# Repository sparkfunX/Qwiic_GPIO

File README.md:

SparkX Qwiic GPIO
=======================================

[*SparkX Qwiic GPIO (SPX-16443)*](https://www.sparkfun.com/products/16443)

TCA9534 breakout board with Qwiic connectors and easy-to-use latch terminals; no longer screw wires into place! Use this board to add more GPIO pins to your system.

Repository Contents
-------------------

* **/Documents** - Contains datasheets and schematic.pdf
* **/Hardware** - Current .brd and .sch files for product
* **/Software** - Examples to get started with Qwiic GPIO

License Information
-------------------

This product is _**open source**_!

Please review the LICENSE.md file for license information.

If you have any questions or concerns on licensing, please contact technical support on our [SparkFun forums](https://forum.sparkfun.com/viewforum.php?f=152).

Distributed as-is; no warranty is given.

- Your friends at SparkFun.

_<COLLABORATION CREDIT>_

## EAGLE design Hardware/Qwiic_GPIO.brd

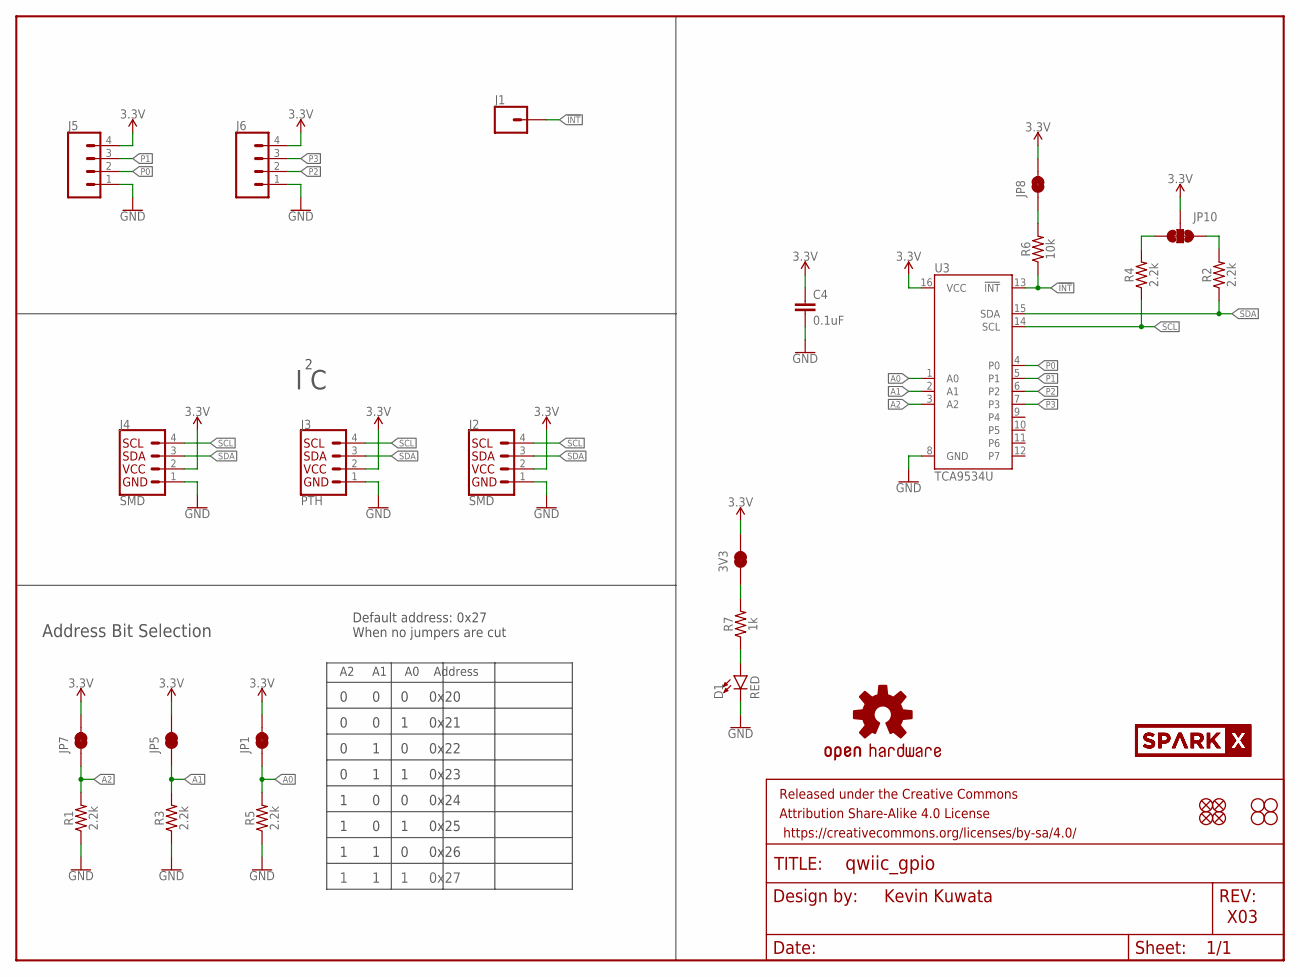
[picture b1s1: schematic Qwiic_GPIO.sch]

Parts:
3V3: JUMPER-SMT_2_NC_TRACE_SILK; SMT-JUMPER_2_NC_TRACE_SILK
C4: 0.1uF; 0603
D1: RED; LED-0603
FD1, FD2: FIDUCIAL1X2; FIDUCIAL-1X2
FRAME1: FRAME-LETTER; CREATIVE_COMMONS
H1, H2: STAND-OFF
J1: CONN_01PTH_NO_SILK_YES_STOP; 1X01_NO_SILK
J2, J4: SMD; 1X04_1MM_RA
J3: PTH; 1X04_NO_SILK
J5, J6: CONN_04LATCH; LATCHTERMINAL-5MM-4
JP1, JP5, JP7, JP8: JUMPER-SMT_2_NC_TRACE_SILK; SMT-JUMPER_2_NC_TRACE_SILK
JP2, JP6: FIDUCIAL1X2; FIDUCIAL-1X2
JP3, JP4: STAND-OFF
JP10: JUMPER-SMT_3_2-NC_TRACE_SILK; SMT-JUMPER_3_2-NC_TRACE_SILK
LOGO1: OSHW-LOGOMINI; OSHW-LOGO-MINI
R1, R2, R3, R4, R5: 2.2k; 0603
R6: 10k; 0603
R7: 1k; 0603
U3: TCA9534U; 16SOIC
U$1, U$2: SPARKX-LOGO3; SPARKX-SMALL

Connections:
3.3V: 3V3.2, C4.1, J2.2 (VCC), J3.2 (VCC), J4.2 (VCC), J5.4, J6.4, JP1.2, JP5.2, JP7.2, JP8.2, JP10.2, U3.16 (VCC)
!INT: J1.1, R6.1, U3.13 (!INT)
A0: JP1.1, R5.2, U3.1 (A0)
A1: JP5.1, R3.2, U3.2 (A1)
A2: JP7.1, R1.2, U3.3 (A2)
GND: C4.2, D1.C, J2.1 (GND), J3.1 (GND), J4.1 (GND), J5.1, J6.1, R1.1, R3.1, R5.1, U3.8 (GND)
unnamed: JP8.1, R6.2
unnamed: D1.A, R7.1
unnamed: 3V3.1, R7.2
P0: J5.2, U3.4 (P0)
P1: J5.3, U3.5 (P1)
P2: J6.2, U3.6 (P2)
P3: J6.3, U3.7 (P3)
SCL: J2.4 (SCL), J3.4 (SCL), J4.4 (SCL), R4.1, U3.14 (SCL)
SCL_PU1: JP10.1, R2.2
SDA: J2.3 (SDA), J3.3 (SDA), J4.3 (SDA), R2.1, U3.15 (SDA)
SDA_PU1: JP10.3, R4.2

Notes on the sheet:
Kevin Kuwata
X03
I C
Address Bit Selection
A2 A1 A0 Address
0 0 0 0x20
0 0 1 0x21
0 1 0 0x22
0 1 1 0x23
1 0 0 0x24
1 0 1 0x25
1 1 0 0x26
1 1 1 0x27
Default address: 0x27 When no jumpers are cut

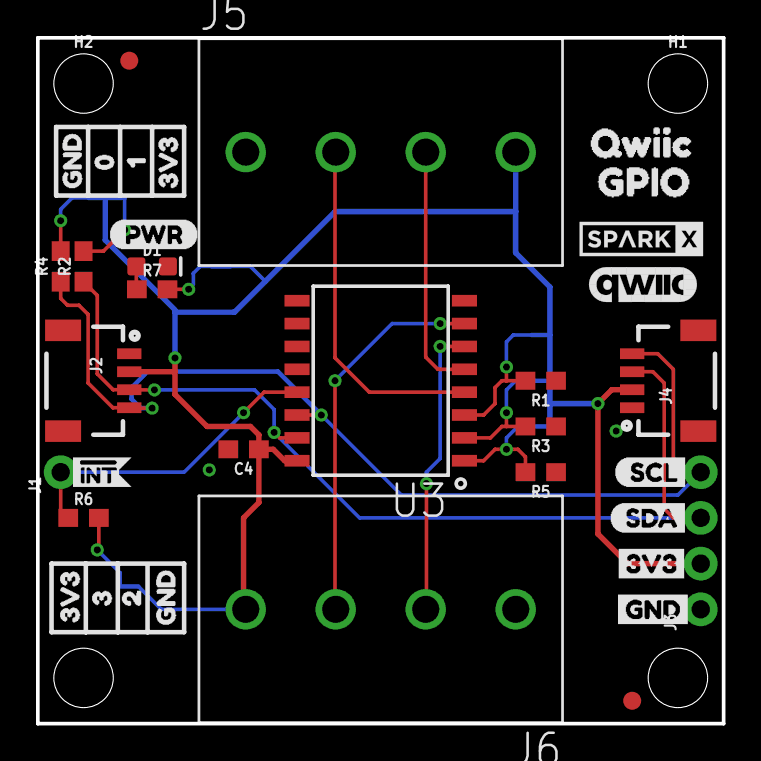
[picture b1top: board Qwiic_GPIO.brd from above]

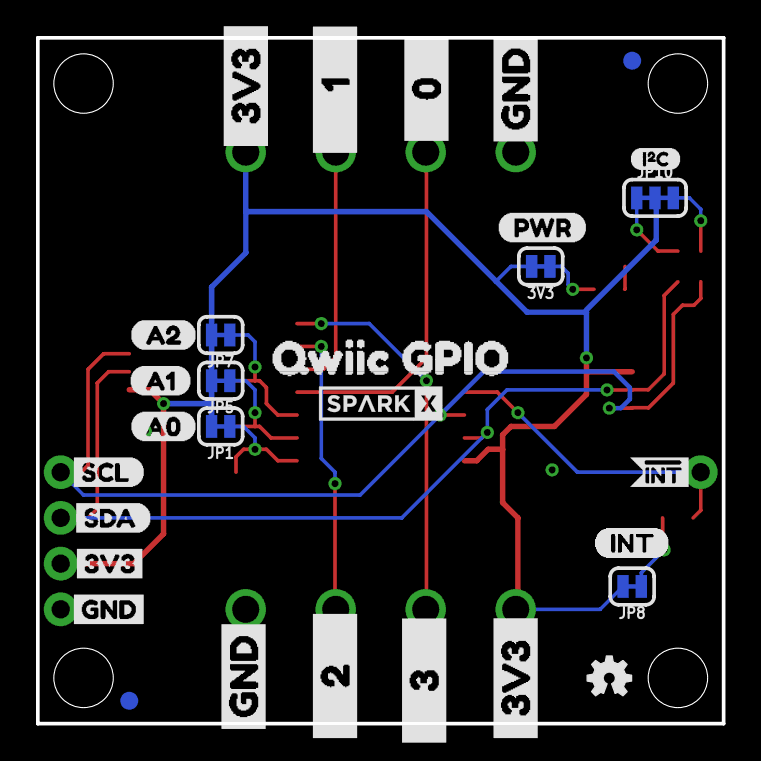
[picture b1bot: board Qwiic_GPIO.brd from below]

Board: 2 copper layers, 38.1 x 38.1 mm, 72 parts (31 on the bottom side), 17 nets.

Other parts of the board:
U$3, U$26, U$38: 3V33
U$5: A11
U$7, U$25: GND4
U$8: QWIIC_GPIO7
U$9: SCL6
U$10: SDA5
U$11: A00
U$12: A21
U$13, U$22: #INT0
U$20: I_SUPER2_C-()-03
U$21: QWIIC_6MM
U$23: SCL0
U$24: SDA1
U$27: 3V32
U$28: GND1
U$29: 15
U$30, U$31: INT1
U$32: QWIIC1
U$33: 20
U$34: 31
U$35: GND2
U$36: GPIO1
U$37: 04
U$39, U$40: PWR0
U$41: ____0____1
U$42: ____2____3
U$43: ____3____4
U$44: _____1____2
U$45, U$46: GND0
U$47, U$48: _3V3_0

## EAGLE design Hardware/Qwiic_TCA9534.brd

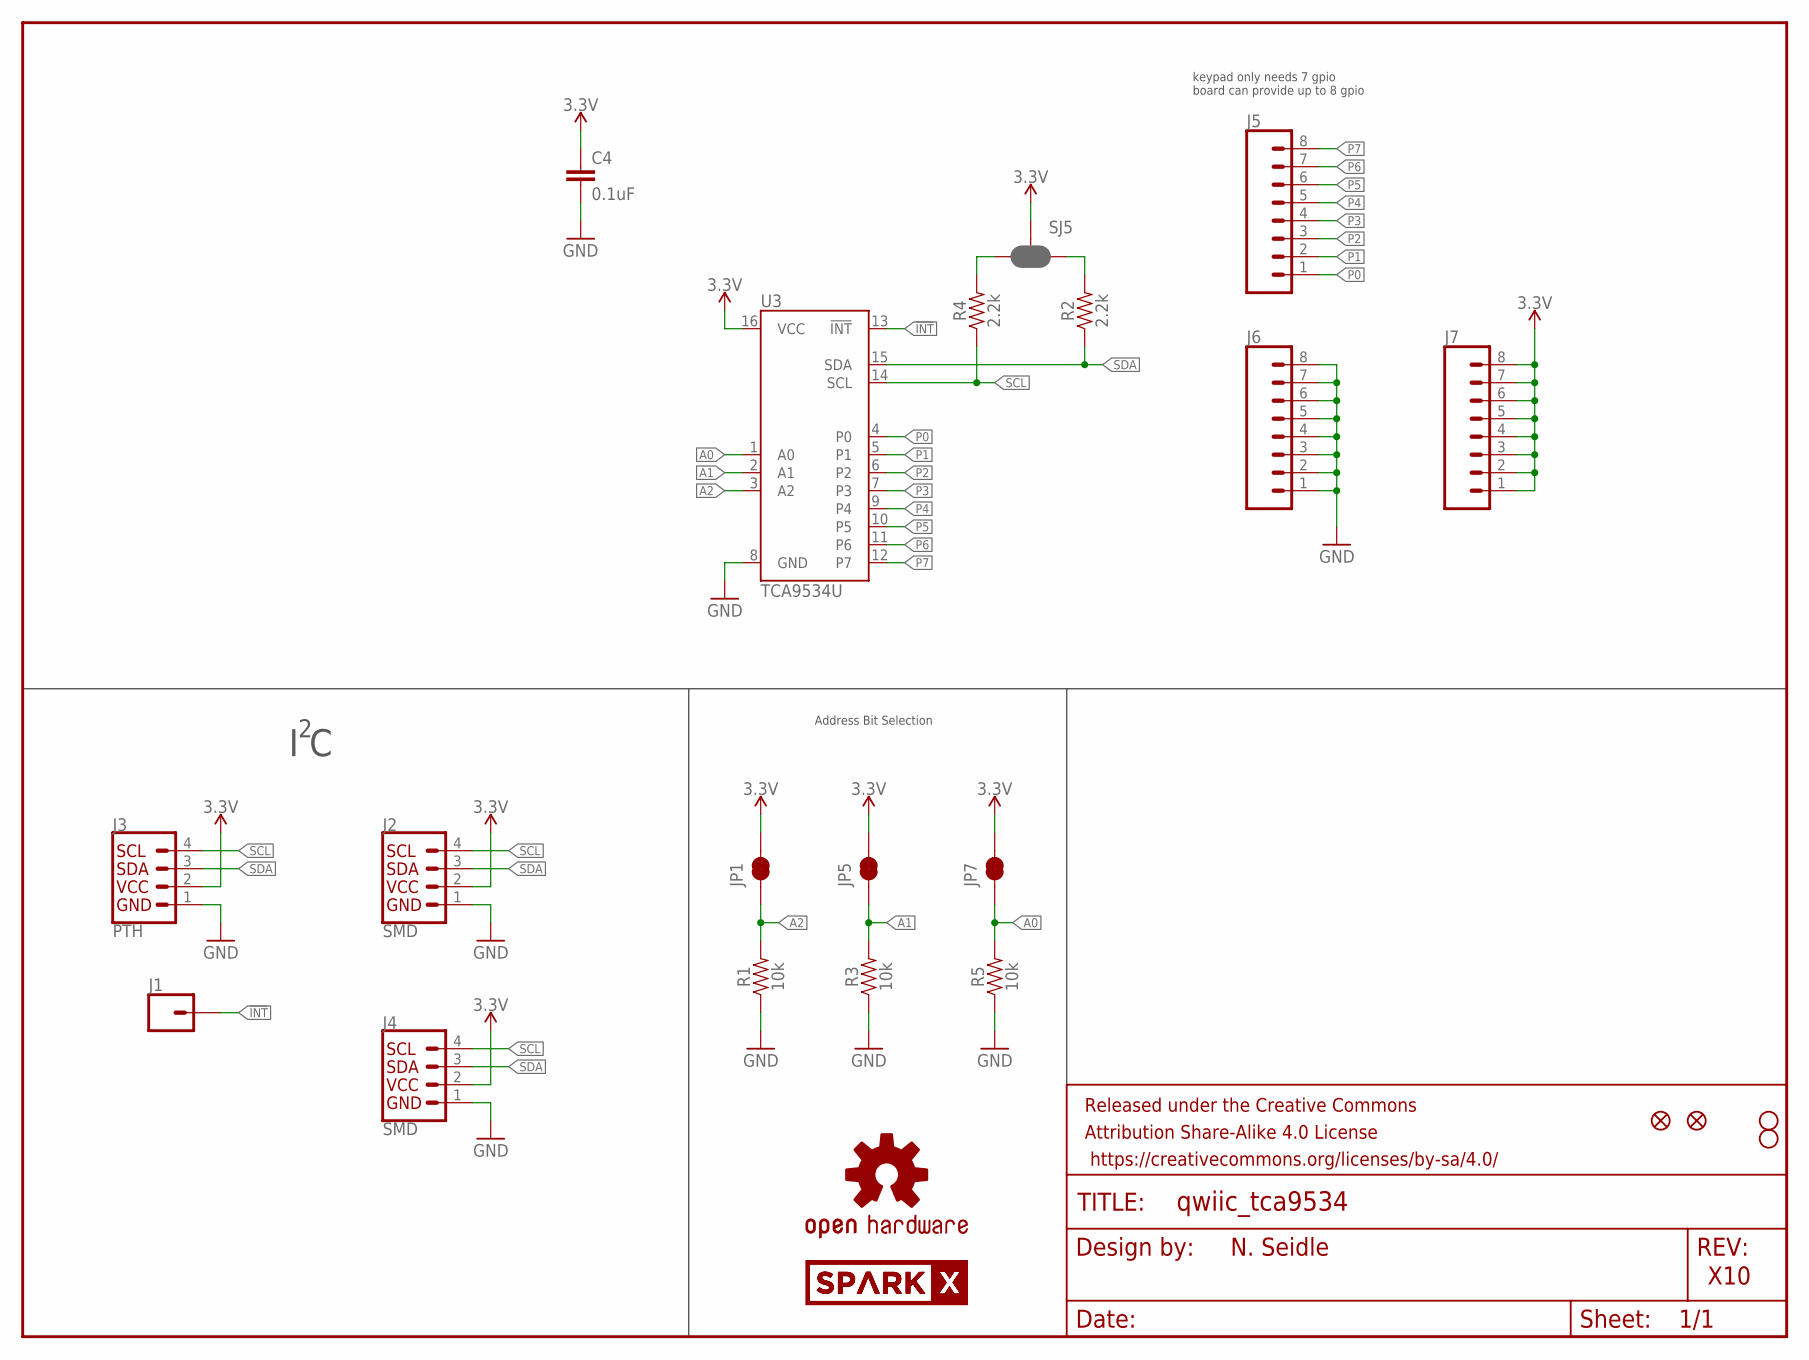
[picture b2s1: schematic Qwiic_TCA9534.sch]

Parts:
C4: 0.1uF; 0603
FRAME1: FRAME-LETTER; CREATIVE_COMMONS
J1: CONN_01PTH_NO_SILK_YES_STOP; 1X01_NO_SILK
J2, J4: SMD; 1X04_1MM_RA
J3: PTH; 1X04_NO_SILK
J5, J6, J7: CONN_08NO_SILK_FEMALE_PTH; 1X08_NO_SILK
JP1, JP5, JP7: JUMPER-SMT_2_NC_TRACE_NO-SILK; SMT-JUMPER_2_NC_TRACE_NO-SILK
JP2, JP6: FIDUCIALUFIDUCIAL; MICRO-FIDUCIAL
JP3, JP4: STAND-OFF
LOGO1: OSHW-LOGOMINI; OSHW-LOGO-MINI
R1, R3, R5: 10k; 0603
R2, R4: 2.2k; 0603
SJ5: SMT-JUMPER-_3-2-NC-PASTE_TALL; SMT-JUMPER_3-2-NC-PASTE_SILK_TALLER_A
U3: TCA9534U; 16SOIC
U$1, U$2: SPARKX-LOGO3; SPARKX-SMALL

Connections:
3.3V: C4.1, J2.2 (VCC), J3.2 (VCC), J4.2 (VCC), J7.1, J7.2, J7.3, J7.4, J7.5, J7.6, J7.7, J7.8, JP1.2, JP5.2, JP7.2, SJ5.2, U3.16 (VCC)
!INT: J1.1, U3.13 (!INT)
A0: JP7.1, R5.2, U3.1 (A0)
A1: JP5.1, R3.2, U3.2 (A1)
A2: JP1.1, R1.2, U3.3 (A2)
GND: C4.2, J2.1 (GND), J3.1 (GND), J4.1 (GND), J6.1, J6.2, J6.3, J6.4, J6.5, J6.6, J6.7, J6.8, R1.1, R3.1, R5.1, U3.8 (GND)
P0: J5.1, U3.4 (P0)
P1: J5.2, U3.5 (P1)
P2: J5.3, U3.6 (P2)
P3: J5.4, U3.7 (P3)
P4: J5.5, U3.9 (P4)
P5: J5.6, U3.10 (P5)
P6: J5.7, U3.11 (P6)
P7: J5.8, U3.12 (P7)
SCL: J2.4 (SCL), J3.4 (SCL), J4.4 (SCL), R4.1, U3.14 (SCL)
SCL_PU1: R2.2, SJ5.1
SDA: J2.3 (SDA), J3.3 (SDA), J4.3 (SDA), R2.1, U3.15 (SDA)
SDA_PU1: R4.2, SJ5.3

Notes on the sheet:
N. Seidle
X10
I C
Address Bit Selection
keypad only needs 7 gpio board can provide up to 8 gpio

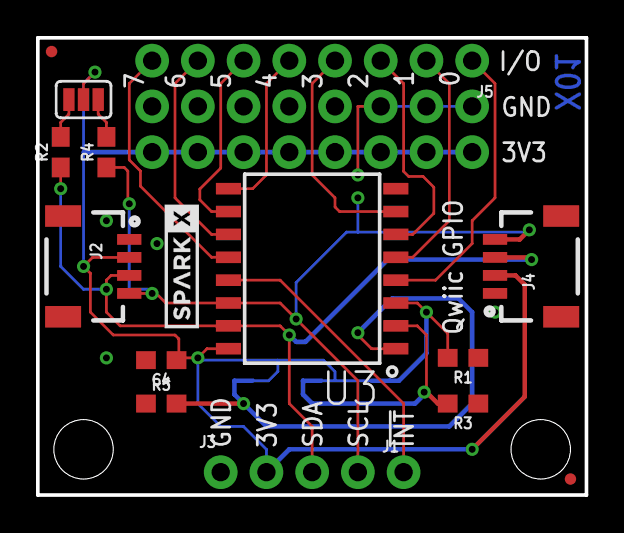
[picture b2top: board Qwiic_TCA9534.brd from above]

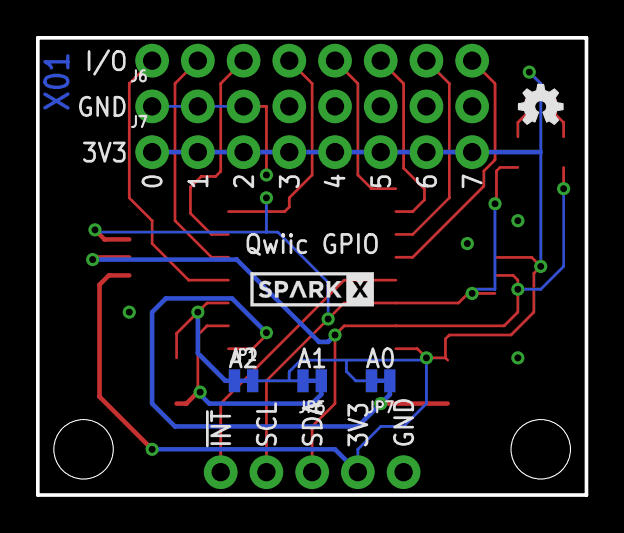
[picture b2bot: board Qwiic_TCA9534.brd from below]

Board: 2 copper layers, 30.5 x 25.4 mm, 26 parts (7 on the bottom side), 18 nets.

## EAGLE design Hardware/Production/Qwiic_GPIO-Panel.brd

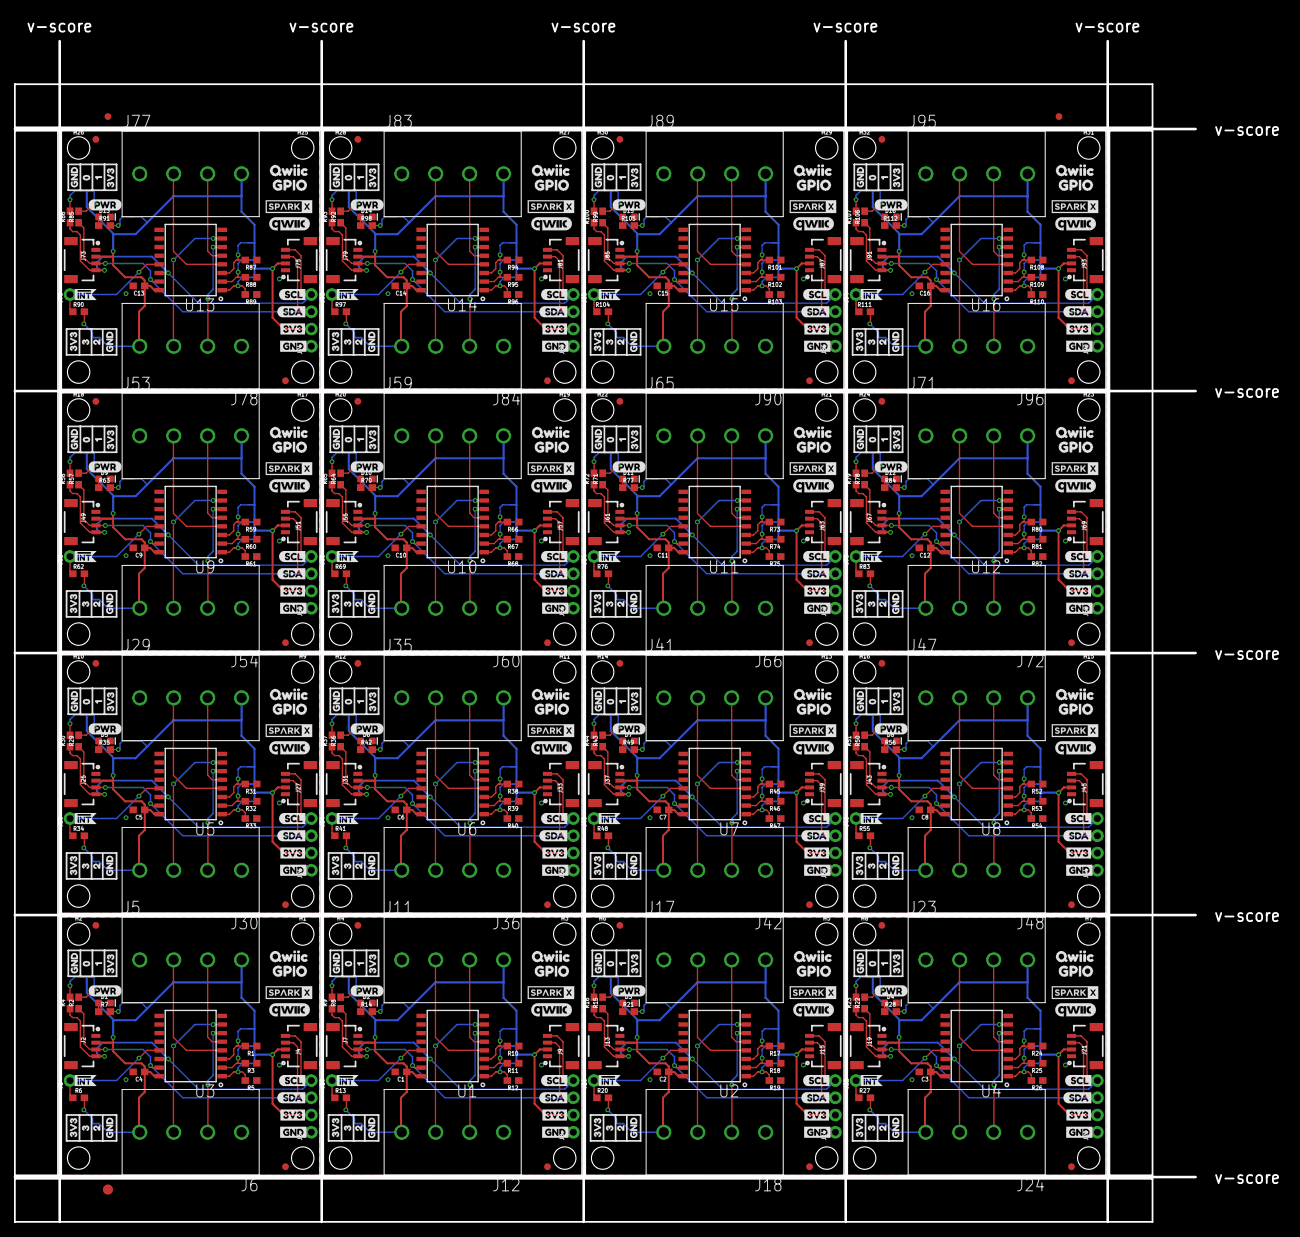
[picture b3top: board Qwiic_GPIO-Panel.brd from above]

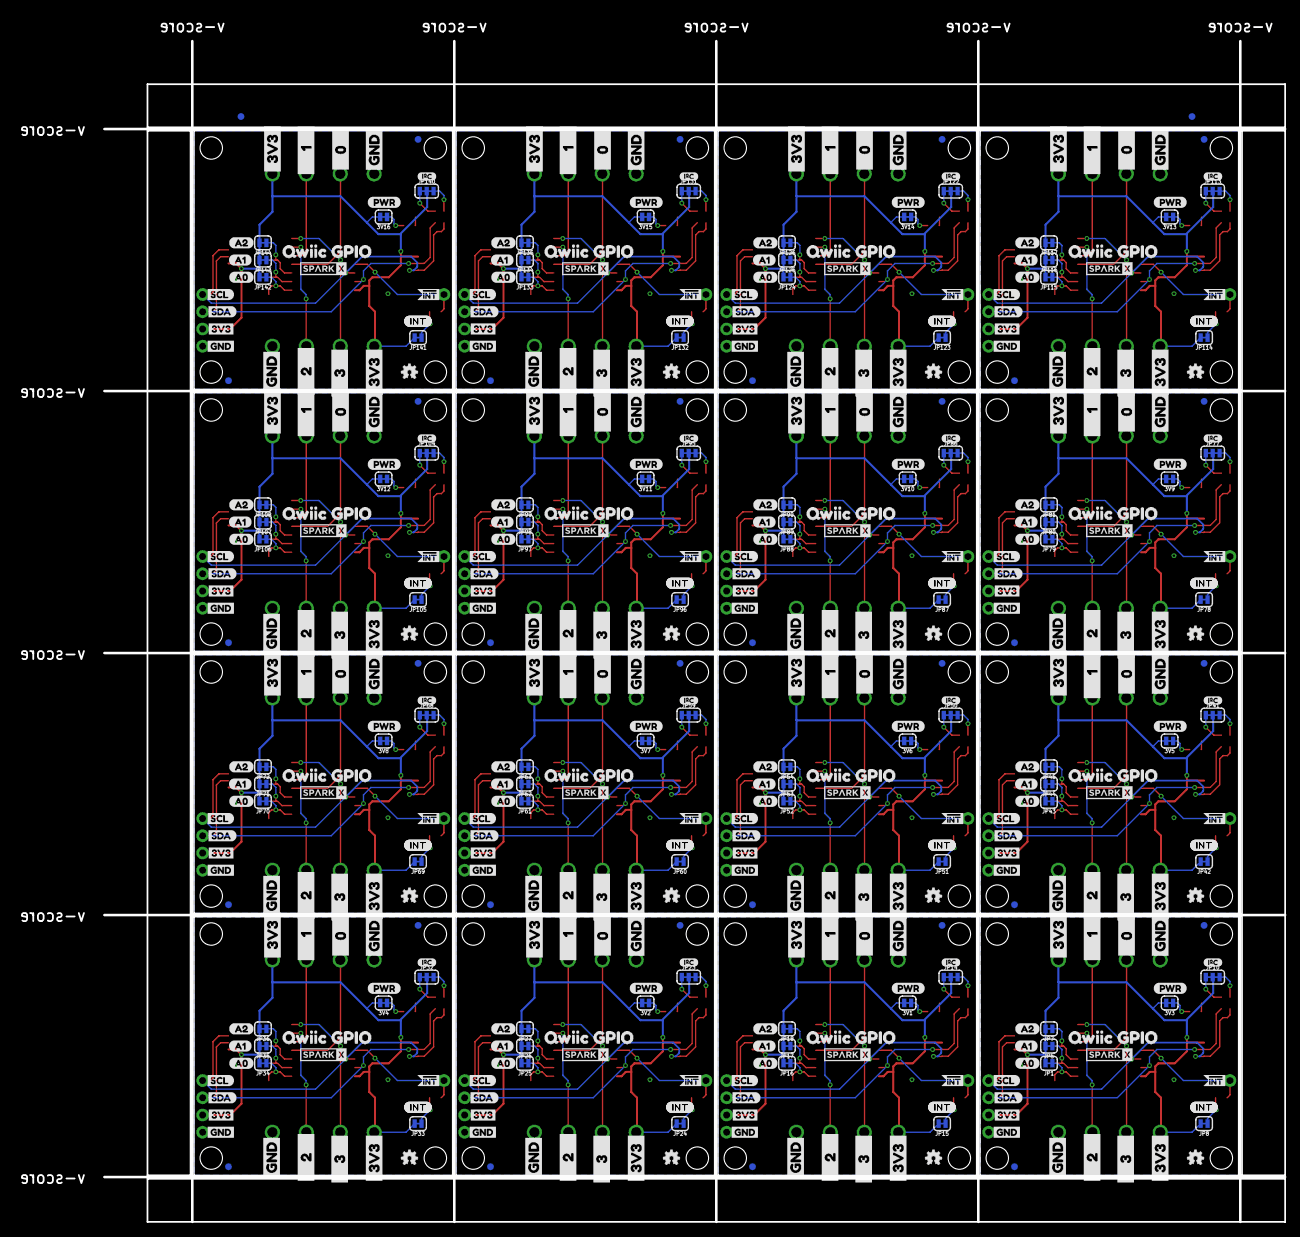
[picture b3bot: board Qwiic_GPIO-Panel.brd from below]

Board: 2 copper layers, 187.2 x 177.9 mm, 1141 parts (498 on the bottom side), 272 nets.

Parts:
3V1, 3V2, 3V3, 3V4, 3V5, 3V6, 3V7, 3V8, 3V9, 3V10, 3V11, 3V12, 3V13, 3V14, 3V15, 3V16: JUMPER-SMT_2_NC_TRACE_SILK; SMT-JUMPER_2_NC_TRACE_SILK
C1, C2, C3, C4, C5, C6, C7, C8, C9, C10, C11, C12, C13, C14, C15, C16: 0.1uF; 0603
D1, D2, D3, D4, D5, D6, D7, D8, D9, D10, D11, D12, D13, D14, D15, D16: RED; LED-0603
E$1, E$2, E$3, E$4: FIDUCIAL-1X2
E$5: FIDUCIAL-1.5X3
FD1, FD2, FD3, FD4, FD5, FD6, FD7, FD8, FD9, FD10, FD11, FD12, FD13, FD14, FD15, FD16, FD17, FD18, FD19, FD20, FD21, FD22, FD23, FD24, FD25, FD26, FD27, FD28, FD29, FD30, FD31, FD32: FIDUCIAL1X2; FIDUCIAL-1X2
H1, H2, H3, H4, H5, H6, H7, H8, H9, H10, H11, H12, H13, H14, H15, H16, H17, H18, H19, H20, H21, H22, H23, H24, H25, H26, H27, H28, H29, H30, H31, H32: STAND-OFF
J1, J10, J16, J22, J28, J34, J40, J46, J52, J58, J64, J70, J76, J82, J88, J94: 1X01_NO_SILK
J2, J4, J7, J9, J13, J15, J19, J21, J25, J27, J31, J33, J37, J39, J43, J45, J49, J51, J55, J57, J61, J63, J67, J69, J73, J75, J79, J81, J85, J87, J91, J93: SMD; 1X04_1MM_RA
J3, J8, J14, J20, J26, J32, J38, J44, J50, J56, J62, J68, J74, J80, J86, J92: PTH; 1X04_NO_SILK
J5, J6, J11, J12, J17, J18, J23, J24, J29, J30, J35, J36, J41, J42, J47, J48, J53, J54, J59, J60, J65, J66, J71, J72, J77, J78, J83, J84, J89, J90, J95, J96: LATCHTERMINAL-5MM-4
JP1, JP5, JP7, JP16, JP17, JP18, JP25, JP26, JP27, JP34, JP35, JP36, JP43, JP44, JP45, JP52, JP53, JP54, JP61, JP62, JP63, JP70, JP71, JP72, JP79, JP80, JP81, JP88, JP89, JP90, JP97, JP98, JP99, JP106, JP107, JP108, JP115, JP116, JP117, JP124, JP125, JP126, JP133, JP134, JP135, JP142, JP143, JP144: SMT-JUMPER_2_NC_TRACE_SILK
JP2, JP6, JP12, JP13, JP21, JP22, JP30, JP31, JP39, JP40, JP48, JP49, JP57, JP58, JP66, JP67, JP75, JP76, JP84, JP85, JP93, JP94, JP102, JP103, JP111, JP112, JP120, JP121, JP129, JP130, JP138, JP139: FIDUCIAL1X2; FIDUCIAL-1X2
JP3, JP4, JP9, JP11, JP19, JP20, JP28, JP29, JP37, JP38, JP46, JP47, JP55, JP56, JP64, JP65, JP73, JP74, JP82, JP83, JP91, JP92, JP100, JP101, JP109, JP110, JP118, JP119, JP127, JP128, JP136, JP137: STAND-OFF
JP8, JP15, JP24, JP33, JP42, JP51, JP60, JP69, JP78, JP87, JP96, JP105, JP114, JP123, JP132, JP141: JUMPER-SMT_2_NC_TRACE_SILK; SMT-JUMPER_2_NC_TRACE_SILK
JP10, JP14, JP23, JP32, JP41, JP50, JP59, JP68, JP77, JP86, JP95, JP104, JP113, JP122, JP131, JP140: JUMPER-SMT_3_2-NC_TRACE_SILK; SMT-JUMPER_3_2-NC_TRACE_SILK
LOGO1, LOGO2, LOGO3, LOGO4, LOGO5, LOGO6, LOGO7, LOGO8, LOGO9, LOGO10, LOGO11, LOGO12, LOGO13, LOGO14, LOGO15, LOGO16: OSHW-LOGOMINI; OSHW-LOGO-MINI
R1, R2, R3, R4, R5, R8, R9, R10, R11, R12, R15, R16, R17, R18, R19, R22, R23, R24, R25, R26, R29, R30, R31, R32, R33, R36, R37, R38, R39, R40, R43, R44, R45, R46, R47, R50, R51, R52, R53, R54, R57, R58, R59, R60, R61, R64, R65, R66, R67, R68, R71, R72, R73, R74, R75, R78, R79, R80, R81, R82, R85, R86, R87, R88, R89, R92, R93, R94, R95, R96, R99, R100, R101, R102, R103, R106, R107, R108, R109, R110: 2.2k; 0603
R6, R13, R20, R27, R34, R41, R48, R55, R62, R69, R76, R83, R90, R97, R104, R111: 10k; 0603
R7, R14, R21, R28, R35, R42, R49, R56, R63, R70, R77, R84, R91, R98, R105, R112: 1k; 0603
U1, U2, U3, U4, U5, U6, U7, U8, U9, U10, U11, U12, U13, U14, U15, U16: TCA9534U; 16SOIC
U$1, U$2, U$4, U$6, U$81, U$82, U$121, U$122, U$161, U$162, U$201, U$202, U$241, U$242, U$281, U$282, U$321, U$322, U$361, U$362, U$401, U$402, U$441, U$442, U$481, U$482, U$521, U$522, U$561, U$562, U$601, U$602: SPARKX-LOGO3; SPARKX-SMALL
U$3, U$14, U$26, U$38, U$56, U$66, U$83, U$96, U$106, U$123, U$136, U$146, U$163, U$176, U$186, U$203, U$216, U$226, U$243, U$256, U$266, U$283, U$296, U$306, U$323, U$336, U$346, U$363, U$376, U$386, U$403, U$416, U$426, U$443, U$456, U$466, U$483, U$496, U$506, U$523, U$536, U$546, U$563, U$576, U$586, U$603, U$616, U$626: 3V33
U$5, U$15, U$84, U$124, U$164, U$204, U$244, U$284, U$324, U$364, U$404, U$444, U$484, U$524, U$564, U$604: A11
U$7, U$16, U$25, U$55, U$85, U$95, U$125, U$135, U$165, U$175, U$205, U$215, U$245, U$255, U$285, U$295, U$325, U$335, U$365, U$375, U$405, U$415, U$445, U$455, U$485, U$495, U$525, U$535, U$565, U$575, U$605, U$615: GND4
U$8, U$17, U$86, U$126, U$166, U$206, U$246, U$286, U$326, U$366, U$406, U$446, U$486, U$526, U$566, U$606: QWIIC_GPIO7
U$9, U$18, U$87, U$127, U$167, U$207, U$247, U$287, U$327, U$367, U$407, U$447, U$487, U$527, U$567, U$607: SCL6
U$10, U$19, U$88, U$128, U$168, U$208, U$248, U$288, U$328, U$368, U$408, U$448, U$488, U$528, U$568, U$608: SDA5
U$11, U$49, U$89, U$129, U$169, U$209, U$249, U$289, U$329, U$369, U$409, U$449, U$489, U$529, U$569, U$609: A00
U$12, U$50, U$90, U$130, U$170, U$210, U$250, U$290, U$330, U$370, U$410, U$450, U$490, U$530, U$570, U$610: A21
U$13, U$22, U$57, U$58, U$97, U$98, U$137, U$138, U$177, U$178, U$217, U$218, U$257, U$258, U$297, U$298, U$337, U$338, U$377, U$378, U$417, U$418, U$457, U$458, U$497, U$498, U$537, U$538, U$577, U$578, U$617, U$618: #INT0
U$20, U$51, U$91, U$131, U$171, U$211, U$251, U$291, U$331, U$371, U$411, U$451, U$491, U$531, U$571, U$611: I_SUPER2_C-()-03
U$21, U$52, U$92, U$132, U$172, U$212, U$252, U$292, U$332, U$372, U$412, U$452, U$492, U$532, U$572, U$612: QWIIC_6MM
U$23, U$53, U$93, U$133, U$173, U$213, U$253, U$293, U$333, U$373, U$413, U$453, U$493, U$533, U$573, U$613: SCL0
U$24, U$54, U$94, U$134, U$174, U$214, U$254, U$294, U$334, U$374, U$414, U$454, U$494, U$534, U$574, U$614: SDA1
U$27, U$67, U$107, U$147, U$187, U$227, U$267, U$307, U$347, U$387, U$427, U$467, U$507, U$547, U$587, U$627: 3V32
U$28, U$68, U$108, U$148, U$188, U$228, U$268, U$308, U$348, U$388, U$428, U$468, U$508, U$548, U$588, U$628: GND1
U$29, U$62, U$102, U$142, U$182, U$222, U$262, U$302, U$342, U$382, U$422, U$462, U$502, U$542, U$582, U$622: 15
U$30, U$31, U$69, U$70, U$109, U$110, U$149, U$150, U$189, U$190, U$229, U$230, U$269, U$270, U$309, U$310, U$349, U$350, U$389, U$390, U$429, U$430, U$469, U$470, U$509, U$510, U$549, U$550, U$589, U$590, U$629, U$630: INT1
U$32, U$59, U$99, U$139, U$179, U$219, U$259, U$299, U$339, U$379, U$419, U$459, U$499, U$539, U$579, U$619: QWIIC1
U$33, U$63, U$103, U$143, U$183, U$223, U$263, U$303, U$343, U$383, U$423, U$463, U$503, U$543, U$583, U$623: 20
U$34, U$64, U$104, U$144, U$184, U$224, U$264, U$304, U$344, U$384, U$424, U$464, U$504, U$544, U$584, U$624: 31
U$35, U$65, U$105, U$145, U$185, U$225, U$265, U$305, U$345, U$385, U$425, U$465, U$505, U$545, U$585, U$625: GND2
U$36, U$60, U$100, U$140, U$180, U$220, U$260, U$300, U$340, U$380, U$420, U$460, U$500, U$540, U$580, U$620: GPIO1
U$37, U$61, U$101, U$141, U$181, U$221, U$261, U$301, U$341, U$381, U$421, U$461, U$501, U$541, U$581, U$621: 04
U$39, U$40, U$71, U$72, U$111, U$112, U$151, U$152, U$191, U$192, U$231, U$232, U$271, U$272, U$311, U$312, U$351, U$352, U$391, U$392, U$431, U$432, U$471, U$472, U$511, U$512, U$551, U$552, U$591, U$592, U$631, U$632: PWR0
U$41, U$73, U$113, U$153, U$193, U$233, U$273, U$313, U$353, U$393, U$433, U$473, U$513, U$553, U$593, U$633: ____0____1
U$42, U$74, U$114, U$154, U$194, U$234, U$274, U$314, U$354, U$394, U$434, U$474, U$514, U$554, U$594, U$634: ____2____3
U$43, U$75, U$115, U$155, U$195, U$235, U$275, U$315, U$355, U$395, U$435, U$475, U$515, U$555, U$595, U$635: ____3____4
U$44, U$76, U$116, U$156, U$196, U$236, U$276, U$316, U$356, U$396, U$436, U$476, U$516, U$556, U$596, U$636: _____1____2
U$45, U$46, U$77, U$78, U$117, U$118, U$157, U$158, U$197, U$198, U$237, U$238, U$277, U$278, U$317, U$318, U$357, U$358, U$397, U$398, U$437, U$438, U$477, U$478, U$517, U$518, U$557, U$558, U$597, U$598, U$637, U$638: GND0
U$47, U$48, U$79, U$80, U$119, U$120, U$159, U$160, U$199, U$200, U$239, U$240, U$279, U$280, U$319, U$320, U$359, U$360, U$399, U$400, U$439, U$440, U$479, U$480, U$519, U$520, U$559, U$560, U$599, U$600, U$639, U$640: _3V3_0

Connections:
3.3V: 3V3.2, C4.1, J2.2, J3.2, J4.2, J5.4, J6.4, JP1.2, JP5.2, JP7.2, JP8.2, JP10.2, U3.16
3.3V1: 3V1.2, C1.1, J7.2, J8.2, J9.2, J11.4, J12.4, JP14.2, JP15.2, JP16.2, JP17.2, JP18.2, U1.16
3.3V2: 3V2.2, C2.1, J13.2, J14.2, J15.2, J17.4, J18.4, JP23.2, JP24.2, JP25.2, JP26.2, JP27.2, U2.16
3.3V3: 3V4.2, C3.1, J19.2, J20.2, J21.2, J23.4, J24.4, JP32.2, JP33.2, JP34.2, JP35.2, JP36.2, U4.16
3.3V4: 3V5.2, C5.1, J25.2, J26.2, J27.2, J29.4, J30.4, JP41.2, JP42.2, JP43.2, JP44.2, JP45.2, U5.16
3.3V5: 3V6.2, C6.1, J31.2, J32.2, J33.2, J35.4, J36.4, JP50.2, JP51.2, JP52.2, JP53.2, JP54.2, U6.16
3.3V6: 3V7.2, C7.1, J37.2, J38.2, J39.2, J41.4, J42.4, JP59.2, JP60.2, JP61.2, JP62.2, JP63.2, U7.16
3.3V7: 3V8.2, C8.1, J43.2, J44.2, J45.2, J47.4, J48.4, JP68.2, JP69.2, JP70.2, JP71.2, JP72.2, U8.16
3.3V8: 3V9.2, C9.1, J49.2, J50.2, J51.2, J53.4, J54.4, JP77.2, JP78.2, JP79.2, JP80.2, JP81.2, U9.16
3.3V9: 3V10.2, C10.1, J55.2, J56.2, J57.2, J59.4, J60.4, JP86.2, JP87.2, JP88.2, JP89.2, JP90.2, U10.16
3.3V10: 3V11.2, C11.1, J61.2, J62.2, J63.2, J65.4, J66.4, JP95.2, JP96.2, JP97.2, JP98.2, JP99.2, U11.16
3.3V11: 3V12.2, C12.1, J67.2, J68.2, J69.2, J71.4, J72.4, JP104.2, JP105.2, JP106.2, JP107.2, JP108.2, U12.16
3.3V12: 3V13.2, C13.1, J73.2, J74.2, J75.2, J77.4, J78.4, JP113.2, JP114.2, JP115.2, JP116.2, JP117.2, U13.16
3.3V13: 3V14.2, C14.1, J79.2, J80.2, J81.2, J83.4, J84.4, JP122.2, JP123.2, JP124.2, JP125.2, JP126.2, U14.16
3.3V14: 3V15.2, C15.1, J85.2, J86.2, J87.2, J89.4, J90.4, JP131.2, JP132.2, JP133.2, JP134.2, JP135.2, U15.16
3.3V15: 3V16.2, C16.1, J91.2, J92.2, J93.2, J95.4, J96.4, JP140.2, JP141.2, JP142.2, JP143.2, JP144.2, U16.16
!INT: J1.1, R6.1, U3.13
!INT1: J10.1, R13.1, U1.13
!INT2: J16.1, R20.1, U2.13
!INT3: J22.1, R27.1, U4.13
!INT4: J28.1, R34.1, U5.13
!INT5: J34.1, R41.1, U6.13
!INT6: J40.1, R48.1, U7.13
!INT7: J46.1, R55.1, U8.13
!INT8: J52.1, R62.1, U9.13
!INT9: J58.1, R69.1, U10.13
!INT10: J64.1, R76.1, U11.13
!INT11: J70.1, R83.1, U12.13
!INT12: J76.1, R90.1, U13.13
!INT13: J82.1, R97.1, U14.13
!INT14: J88.1, R104.1, U15.13
!INT15: J94.1, R111.1, U16.13
A0: JP1.1, R5.2, U3.1
A1: JP5.1, R3.2, U3.2
A2: JP7.1, R1.2, U3.3
A3: JP16.1, R12.2, U1.1
A4: JP17.1, R11.2, U1.2
A5: JP18.1, R10.2, U1.3
A6: JP25.1, R19.2, U2.1
A7: JP26.1, R18.2, U2.2
A8: JP27.1, R17.2, U2.3
A9: JP34.1, R26.2, U4.1
A10: JP35.1, R25.2, U4.2
A11: JP36.1, R24.2, U4.3
A12: JP43.1, R33.2, U5.1
A13: JP44.1, R32.2, U5.2
A14: JP45.1, R31.2, U5.3
A15: JP52.1, R40.2, U6.1
A16: JP53.1, R39.2, U6.2
A17: JP54.1, R38.2, U6.3
A18: JP61.1, R47.2, U7.1
A19: JP62.1, R46.2, U7.2
A20: JP63.1, R45.2, U7.3
A21: JP70.1, R54.2, U8.1
A22: JP71.1, R53.2, U8.2
A23: JP72.1, R52.2, U8.3
A24: JP79.1, R61.2, U9.1
A25: JP80.1, R60.2, U9.2
A26: JP81.1, R59.2, U9.3
A27: JP88.1, R68.2, U10.1
A28: JP89.1, R67.2, U10.2
A29: JP90.1, R66.2, U10.3
A30: JP97.1, R75.2, U11.1
A31: JP98.1, R74.2, U11.2
A32: JP99.1, R73.2, U11.3
A33: JP106.1, R82.2, U12.1
A34: JP107.1, R81.2, U12.2
A35: JP108.1, R80.2, U12.3
A36: JP115.1, R89.2, U13.1
A37: JP116.1, R88.2, U13.2
A38: JP117.1, R87.2, U13.3
A39: JP124.1, R96.2, U14.1
A40: JP125.1, R95.2, U14.2
A41: JP126.1, R94.2, U14.3
A42: JP133.1, R103.2, U15.1
A43: JP134.1, R102.2, U15.2
A44: JP135.1, R101.2, U15.3
A45: JP142.1, R110.2, U16.1
A46: JP143.1, R109.2, U16.2
A47: JP144.1, R108.2, U16.3
GND: C4.2, D1.C, J2.1, J3.1, J4.1, J5.1, J6.1, R1.1, R3.1, R5.1, U3.8
GND1: C1.2, D2.C, J7.1, J8.1, J9.1, J11.1, J12.1, R10.1, R11.1, R12.1, U1.8
GND2: C2.2, D3.C, J13.1, J14.1, J15.1, J17.1, J18.1, R17.1, R18.1, R19.1, U2.8
GND3: C3.2, D4.C, J19.1, J20.1, J21.1, J23.1, J24.1, R24.1, R25.1, R26.1, U4.8
GND4: C5.2, D5.C, J25.1, J26.1, J27.1, J29.1, J30.1, R31.1, R32.1, R33.1, U5.8
GND5: C6.2, D6.C, J31.1, J32.1, J33.1, J35.1, J36.1, R38.1, R39.1, R40.1, U6.8
GND6: C7.2, D7.C, J37.1, J38.1, J39.1, J41.1, J42.1, R45.1, R46.1, R47.1, U7.8
GND7: C8.2, D8.C, J43.1, J44.1, J45.1, J47.1, J48.1, R52.1, R53.1, R54.1, U8.8
GND8: C9.2, D9.C, J49.1, J50.1, J51.1, J53.1, J54.1, R59.1, R60.1, R61.1, U9.8
GND9: C10.2, D10.C, J55.1, J56.1, J57.1, J59.1, J60.1, R66.1, R67.1, R68.1, U10.8
GND10: C11.2, D11.C, J61.1, J62.1, J63.1, J65.1, J66.1, R73.1, R74.1, R75.1, U11.8
GND11: C12.2, D12.C, J67.1, J68.1, J69.1, J71.1, J72.1, R80.1, R81.1, R82.1, U12.8
GND12: C13.2, D13.C, J73.1, J74.1, J75.1, J77.1, J78.1, R87.1, R88.1, R89.1, U13.8
GND13: C14.2, D14.C, J79.1, J80.1, J81.1, J83.1, J84.1, R94.1, R95.1, R96.1, U14.8
GND14: C15.2, D15.C, J85.1, J86.1, J87.1, J89.1, J90.1, R101.1, R102.1, R103.1, U15.8
GND15: C16.2, D16.C, J91.1, J92.1, J93.1, J95.1, J96.1, R108.1, R109.1, R110.1, U16.8
unnamed: JP8.1, R6.2
unnamed: D1.A, R7.1
unnamed: 3V3.1, R7.2
unnamed: JP15.1, R13.2
unnamed: D2.A, R14.1
unnamed: 3V1.1, R14.2
unnamed: JP24.1, R20.2
unnamed: D3.A, R21.1
unnamed: 3V2.1, R21.2
unnamed: JP33.1, R27.2
unnamed: D4.A, R28.1
unnamed: 3V4.1, R28.2
unnamed: JP42.1, R34.2
unnamed: D5.A, R35.1
unnamed: 3V5.1, R35.2
unnamed: JP51.1, R41.2
unnamed: D6.A, R42.1
unnamed: 3V6.1, R42.2
unnamed: JP60.1, R48.2
unnamed: D7.A, R49.1
unnamed: 3V7.1, R49.2
unnamed: JP69.1, R55.2
unnamed: D8.A, R56.1
unnamed: 3V8.1, R56.2
unnamed: JP78.1, R62.2
unnamed: D9.A, R63.1
unnamed: 3V9.1, R63.2
unnamed: JP87.1, R69.2
unnamed: D10.A, R70.1
unnamed: 3V10.1, R70.2
unnamed: JP96.1, R76.2
unnamed: D11.A, R77.1
unnamed: 3V11.1, R77.2
unnamed: JP105.1, R83.2
unnamed: D12.A, R84.1
unnamed: 3V12.1, R84.2
unnamed: JP114.1, R90.2
unnamed: D13.A, R91.1
unnamed: 3V13.1, R91.2
unnamed: JP123.1, R97.2
unnamed: D14.A, R98.1
unnamed: 3V14.1, R98.2
unnamed: JP132.1, R104.2
unnamed: D15.A, R105.1
unnamed: 3V15.1, R105.2
unnamed: JP141.1, R111.2
unnamed: D16.A, R112.1
unnamed: 3V16.1, R112.2
P0: J5.2, U3.4
P1: J5.3, U3.5
P2: J6.2, U3.6
P3: J6.3, U3.7
P4: J11.2, U1.4
P5: J12.2, U1.6
P6: J12.3, U1.7
P7: J11.3, U1.5
P8: J17.2, U2.4
P9: J18.2, U2.6
P10: J18.3, U2.7
P11: J17.3, U2.5
P12: J23.2, U4.4
P13: J24.2, U4.6
P14: J24.3, U4.7
P15: J23.3, U4.5
P16: J29.2, U5.4
P17: J30.2, U5.6
P18: J30.3, U5.7
P19: J29.3, U5.5
P20: J35.2, U6.4
P21: J36.2, U6.6
P22: J36.3, U6.7
P23: J35.3, U6.5
P24: J41.2, U7.4
P25: J42.2, U7.6
P26: J42.3, U7.7
P27: J41.3, U7.5
P28: J47.2, U8.4
P29: J48.2, U8.6
P30: J48.3, U8.7
P31: J47.3, U8.5
P32: J53.2, U9.4
P33: J54.2, U9.6
P34: J54.3, U9.7
P35: J53.3, U9.5
P36: J59.2, U10.4
P37: J60.2, U10.6
P38: J60.3, U10.7
P39: J59.3, U10.5
P40: J65.2, U11.4
P41: J66.2, U11.6
P42: J66.3, U11.7
P43: J65.3, U11.5
P44: J71.2, U12.4
P45: J72.2, U12.6
P46: J72.3, U12.7
P47: J71.3, U12.5
P48: J77.2, U13.4
P49: J78.2, U13.6
P50: J78.3, U13.7
P51: J77.3, U13.5
P52: J83.2, U14.4
P53: J84.2, U14.6
P54: J84.3, U14.7
P55: J83.3, U14.5
P56: J89.2, U15.4
P57: J90.2, U15.6
P58: J90.3, U15.7
P59: J89.3, U15.5
P60: J95.2, U16.4
P61: J96.2, U16.6
P62: J96.3, U16.7
P63: J95.3, U16.5
SCL: J2.4, J3.4, J4.4, R4.1, U3.14
SCL1: J7.4, J8.4, J9.4, R9.1, U1.14
SCL2: J13.4, J14.4, J15.4, R16.1, U2.14
SCL3: J19.4, J20.4, J21.4, R23.1, U4.14
SCL4: J25.4, J26.4, J27.4, R30.1, U5.14
SCL5: J31.4, J32.4, J33.4, R37.1, U6.14
SCL6: J37.4, J38.4, J39.4, R44.1, U7.14
SCL7: J43.4, J44.4, J45.4, R51.1, U8.14
SCL8: J49.4, J50.4, J51.4, R58.1, U9.14
SCL9: J55.4, J56.4, J57.4, R65.1, U10.14
SCL10: J61.4, J62.4, J63.4, R72.1, U11.14
SCL11: J67.4, J68.4, J69.4, R79.1, U12.14
SCL12: J73.4, J74.4, J75.4, R86.1, U13.14
SCL13: J79.4, J80.4, J81.4, R93.1, U14.14
SCL14: J85.4, J86.4, J87.4, R100.1, U15.14
SCL15: J91.4, J92.4, J93.4, R107.1, U16.14
SCL_PU1: JP10.1, R2.2
SCL_PU2: JP14.1, R8.2
SCL_PU3: JP23.1, R15.2
SCL_PU4: JP32.1, R22.2
SCL_PU5: JP41.1, R29.2
SCL_PU6: JP50.1, R36.2
SCL_PU7: JP59.1, R43.2
SCL_PU8: JP68.1, R50.2
SCL_PU9: JP77.1, R57.2
SCL_PU10: JP86.1, R64.2
SCL_PU11: JP95.1, R71.2
SCL_PU12: JP104.1, R78.2
SCL_PU13: JP113.1, R85.2
SCL_PU14: JP122.1, R92.2
SCL_PU15: JP131.1, R99.2
SCL_PU16: JP140.1, R106.2
SDA: J2.3, J3.3, J4.3, R2.1, U3.15
SDA1: J7.3, J8.3, J9.3, R8.1, U1.15
SDA2: J13.3, J14.3, J15.3, R15.1, U2.15
SDA3: J19.3, J20.3, J21.3, R22.1, U4.15
SDA4: J25.3, J26.3, J27.3, R29.1, U5.15
SDA5: J31.3, J32.3, J33.3, R36.1, U6.15
SDA6: J37.3, J38.3, J39.3, R43.1, U7.15
SDA7: J43.3, J44.3, J45.3, R50.1, U8.15
SDA8: J49.3, J50.3, J51.3, R57.1, U9.15
SDA9: J55.3, J56.3, J57.3, R64.1, U10.15
SDA10: J61.3, J62.3, J63.3, R71.1, U11.15
SDA11: J67.3, J68.3, J69.3, R78.1, U12.15
SDA12: J73.3, J74.3, J75.3, R85.1, U13.15
SDA13: J79.3, J80.3, J81.3, R92.1, U14.15
SDA14: J85.3, J86.3, J87.3, R99.1, U15.15
SDA15: J91.3, J92.3, J93.3, R106.1, U16.15
SDA_PU1: JP10.3, R4.2
SDA_PU2: JP14.3, R9.2
SDA_PU3: JP23.3, R16.2
SDA_PU4: JP32.3, R23.2
SDA_PU5: JP41.3, R30.2
SDA_PU6: JP50.3, R37.2
SDA_PU7: JP59.3, R44.2
SDA_PU8: JP68.3, R51.2
SDA_PU9: JP77.3, R58.2
SDA_PU10: JP86.3, R65.2
SDA_PU11: JP95.3, R72.2
SDA_PU12: JP104.3, R79.2
SDA_PU13: JP113.3, R86.2
SDA_PU14: JP122.3, R93.2
SDA_PU15: JP131.3, R100.2
SDA_PU16: JP140.3, R107.2

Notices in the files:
parts and their libraries:
SparkFun-Resistors: Licensing: Creative Commons ShareAlike 4.0 International - https://creativecommons.org/licenses/by-sa/4.0
SparkFun-Aesthetics: Released under the Creative Commons Attribution Share-Alike 4.0 License
SparkFun-Aesthetics: https://creativecommons.org/licenses/by-sa/4.0
